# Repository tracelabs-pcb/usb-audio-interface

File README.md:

USB-C Audio Interface — Desktop / Streaming / Meetings

**Status: PCB-Design abgeschlossen — unbestückt**  
**Tool:** KiCad | **Layer:** 4-Layer | **Hersteller-ready:** Ja

---

## Projektbeschreibung

Kompaktes USB-C Audio-Interface für Desktop, Streaming und Meetings.
Wird am PC/Mac/Linux als Standard-USB-Audio-Device (UAC2) erkannt,
ohne Treiber. Entwickelt als reproduzierbarer Prototyp mit sauberem
Mixed-Signal-Layout (Analog + Digital).

**Besonderheiten:**
- USB Audio Class 2 (UAC2) — Plug & Play, treiberlos
- Stereo Kopfhörerverstärker mit I²C-Lautstärkeregelung (DirectPath)
- Elektret-Mikrofon-Bias + Hardware-Mute
- Rotary Encoder für Lautstärke + Mute
- Getrennte Digital/Analog-Versorgung (Buck → 3V3D → LDO → 3V3A)
- ESD-Schutz USB + Audio
- Testpunkte für alle kritischen Rails und Signale

---

## Hardware

| Komponente | Beschreibung |
|---|---|
| USB Audio Codec | PCM2912APJTR (ADC + DAC, USB-Enumeration integriert) |
| Kopfhörerverstärker | TPA6130A2RTJR (Stereo, I²C Volume, DirectPath/Capless) |
| Steuer-MCU | ATtiny1616 (Encoder, I²C, Button Handling) |
| Buck Converter | TPS62150A (5V → 3.3V Digital) |
| Analog LDO | TPS7A2033PDBVR (3.3V Digital → 3.3V Analog, Low-Noise) |
| ESD-Schutz | TPD4E05U06DQAR (USB, Audio, GPIO) |
| Stackup | 4-Layer (Signal / GND-Plane / Power / Signal+Pour) |
| Tool | KiCad |

---

## Anschlüsse

- USB-C  — Daten + Versorgung (Bus-Powered)
- TRRS 3.5mm Klinke CTIA (Headset: Mic + L/R + GND)
- Rotary Encoder (Lautstärke + Mute)
- LEDs: Power, Mic-Mute, Clip/Status
- I²C Header (OLED / Erweiterung)
- GPIO Header
- UPDI Header (ATtiny Programmierung)

---

## Architektur

**Versorgung:**
USB 5V → Buck (TPS62150A) → 3V3 Digital → LDO (TPS7A2033) → 3V3 Analog

**Signalführung:**
- USB D+/D− als Differential Pair
- Audio-Pfade kurz, getrennt von Digital
- Keine GND-Splits — gemeinsame GND-Plane (L2 durchgehend)

**Testpunkte:** 5V, 3V3D, 3V3A, GND, USB D+/D−, Audio-Nodes

---

## Ausschlüsse

Kein Serienprodukt — kein CE/EMV, keine Normenfreigabe,
keine sicherheitskritischen Funktionen.

---

## Dateien in diesem Repository

- `/kicad/` — KiCad Projektdateien
- `/screenshots/` — PCB- und Schematic-Ansichten

---

> Entwickelt von [Shawn Schneider](https://tracelabs-pcb.de)  
> — PCB-Design & Lötservice, Wolfsburg

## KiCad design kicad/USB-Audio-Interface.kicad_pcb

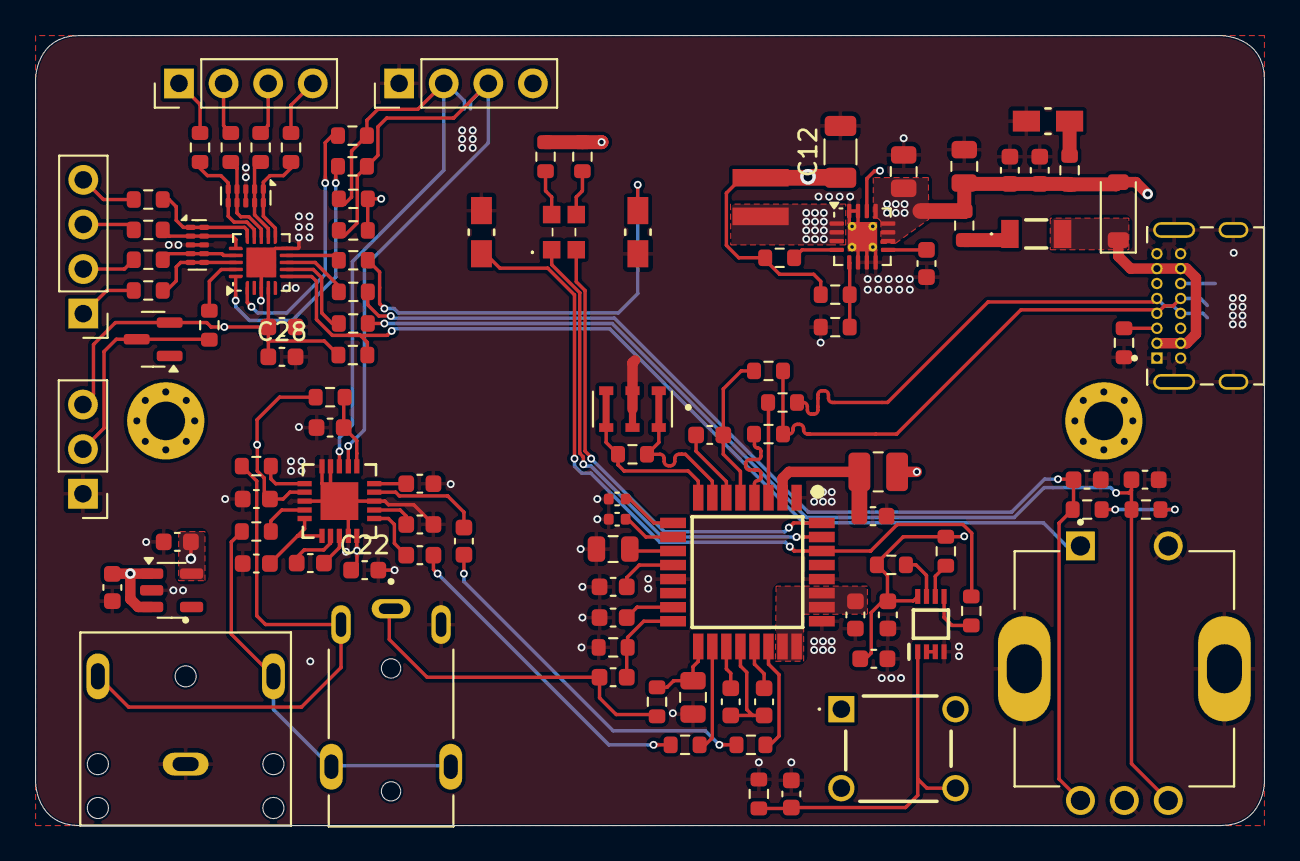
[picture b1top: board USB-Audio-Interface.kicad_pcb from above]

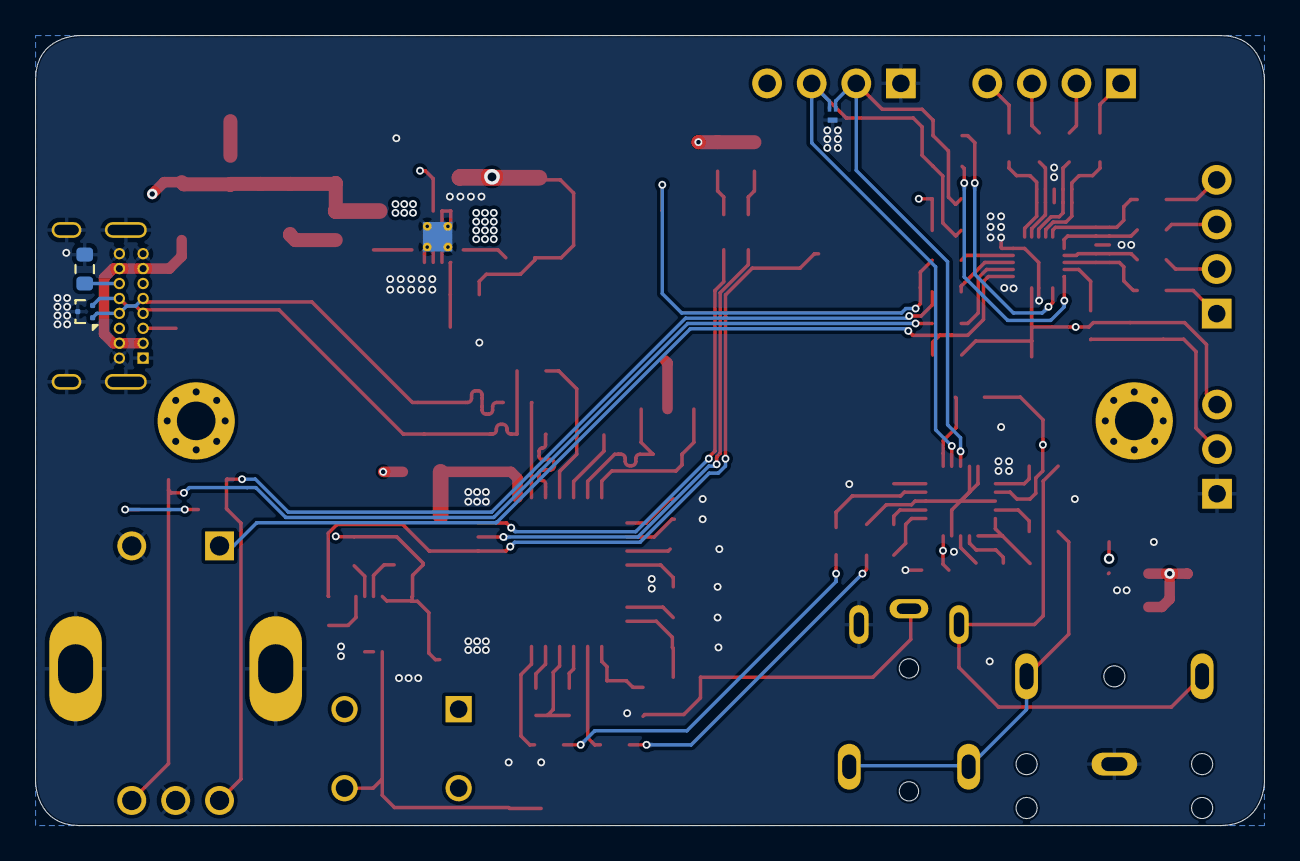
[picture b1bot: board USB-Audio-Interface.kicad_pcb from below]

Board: 4 copper layers, 70.0 x 45.0 mm, 108 parts (3 on the bottom side), 89 nets.

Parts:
C1, C2: 100pF; C_0402_1005Metric
C3, C21: 3,3µF; C_0805_2012Metric
C4, C22#2, C23, C24, C27, C33, C38: 100nF; C_0603_1608Metric
C5, C6, C7, C13, C14, C16, C17, C18, C19, C22, C28, C32, C37: 1µF; C_0603_1608Metric
C8, C36: 10µF; C_0805_2012Metric
C11: 3,3nF; C_0603_1608Metric
C12: 22µF; C_1206_3216Metric
C15: 1uF; C_0603_1608Metric
C20: 220nF; C_0603_1608Metric
C25, C26, C29, C31: 0,47µF; C_0603_1608Metric
C34, C35: 10nF; C_0603_1608Metric
CR1: PESD5V0X2UAMB; DFN10006B-3_SOT883B_NEX
D1, D4: RED; SM0805HCL_BIV
D3: BAT54A; SOT-23
D6: Littelfuse SMF5.0A; D_SOD-123
D7: Green_PWR; SM0805HCL_BIV
F1: MF-NSMF075/13X-2; MFNSMF07513X2
FB1: BLM18PG121SN1D; R_0603_1608Metric
IC1: PCM2912APJTR; QFP80P900X900X120-32N
IC2: TPS7A2033PDBVR; SOT-23-5
IC3: 74LVC1G74DC,125; SOP50P310X100-8N
J1: FC68125; CLIFF_FC68125
J3: SJ1-3523N; CUI_SJ1-3523N
J4: Conn_01x03_Pin; PinHeader_1x03_P2.54mm_Vertical
J5, J6, J7: Conn_01x04_Pin; PinHeader_1x04_P2.54mm_Vertical
J8: UJ20-C-H-G-SMT-TR; CUI_UJ20-C-H-G-SMT-TR
L1: 1µH; L_1008_2520Metric
L2: 2,2µH | WÜ 744028002; WE-TPC_282892
LED1: 150080RV54050
R1, R2, R23, R24: 22Ω; R_0603_1608Metric
R3, R4, R5: 1,5kΩ; R_0603_1608Metric
R8, R14, R19, R28: 100kΩ; R_0603_1608Metric
R9: 1,21MΩ; R_0603_1608Metric
R10: 383kΩ; R_0603_1608Metric
R11: 1MΩ; R_0603_1608Metric
R12, R13: 33Ω; R_0603_1608Metric
R15, R21: 4,7Ω; R_0603_1608Metric
R16: 2,2kΩ; R_0603_1608Metric
R17, R18, R29, R30, R33: 10kΩ; R_0603_1608Metric
R20, R22: 430Ω; R_0603_1608Metric
R25, R26, R27: 4,7kΩ; R_0603_1608Metric
R31, R32, R35, R36, R37, R38, R39, R40, R41, R42: 100Ω; R_0603_1608Metric
R43, R44: 5,1kΩ; R_0603_1608Metric
R45: 910Ω; R_0603_1608Metric
S2: PEC11R-4220F-S0024; XDCR_PEC11R-4220F-S0024
S3: TS02-66-120-BK-160-LCR-D; TS0266120BK160LCRD
U1: ATtiny1616-M; VQFN-20-1EP_3x3mm_P0.4mm_EP1.7x1.7mm
U2: TPA6130A2RTJR; QFN50P400X400X80-21N
U3: TPD2EUSB30; Texas_DRT-3
U4: TPS62150A; VQFN-16-1EP_3x3mm_P0.5mm_EP1.68x1.68mm_ThermalVias
U7, U8: TPD4E05U06DQA; USON-10_2.5x1.0mm_P0.5mm
Y1: CSTCR6M00G55Z-R0; OSC_CSTCR6M00G55Z-R0

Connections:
+5V: C8.1, C13.1, C36.1, C37.1, C38.1, D6.2 (A2), FB1.2, IC2.1 (IN), IC2.3 (EN), L1.1, R4.1, R5.1, R45.2, U4.10 (VIN), U4.11 (VIN), U4.12 (VIN), U4.13 (EN)
AUDIO_MUTE: R33.1, S2.1, U1.6 (PA5)
I2C_SCL_3V3: CR1.1, J5.2, R13.2, R27.1, U2.8 (SCL)
I2C_SDA_3V3: CR1.2, J5.3, R12.2, R26.1, U2.7 (SDA)
MCU_VCC: C12.1, C22#2.1, C23.1, C27.1, C28.1, D3.2, IC3.8 (VCC), J4.3, J5.4, L2.2, R8.1, R9.1, R17.1, R18.1, R26.2, R27.2, R29.2, R30.2, R33.2, S3.1, U1.4 (VCC), U4.14 (VOS)
MIC: C20.2, J1.1, R16.2
MMUTE: D1.2 (A), IC1.30 (MMUTE), R20.2
unnamed: D4.2 (A), R22.2
unnamed: D7.2 (A), R45.1
unnamed: F1.1, FB1.1
unnamed: IC1.4 (D+), R2.2
unnamed: IC1.3 (D-), R1.2
unnamed: C7.1, IC1.6 (DGND)
unnamed: C1.1, IC1.9 (FL)
unnamed: C2.1, IC1.10 (FR)
unnamed: C16.2, C17.1, IC1.20 (HGND)
unnamed: C21.1, IC1.17 (MBIAS), R16.1
unnamed: C6.1, IC1.2 (VBUS), L1.2
unnamed: C5.1, IC1.15 (VCCA)
unnamed: C17.2, IC1.19 (VCCL)
unnamed: C16.1, IC1.21 (VCCR)
unnamed: C3.1, IC1.11 (VCOM1)
unnamed: C4.1, IC1.12 (VCOM2)
unnamed: C7.2, IC1.5 (VDD), R3.2
unnamed: C20.1, IC1.16 (VIN), R28.2
unnamed: IC1.18 (VOUTL), R24.2
unnamed: IC1.22 (VOUTR), R23.2
unnamed: IC1.8 (XTI), R11.1, Y1.3
unnamed: IC1.7 (XTO), R11.2, Y1.1
unnamed: IC1.32 (~PLAY), LED1.2 (K_V)
unnamed: IC1.31 (~REC), LED1.1 (K_R)
unnamed: C24.1, IC3.1 (CP), R19.1, S3.4
unnamed: IC3.2 (D), IC3.3 (~Q)
unnamed: IC3.5 (Q), R20.1
unnamed: IC3.6 (~RD), R18.2
unnamed: IC3.7 (~SD), R17.2
unnamed: J6.1, R35.1
unnamed: J6.2, R36.1
unnamed: J6.3, R37.1
unnamed: J6.4, R38.1
unnamed: J7.1, R39.1
unnamed: J7.2, R40.1
unnamed: J7.3, R41.1
unnamed: J7.4, R42.1
unnamed: J8.A5 (CC1), R44.1
unnamed: J8.B5 (CC2), R43.1
unnamed: L2.1, U4.1 (SW), U4.2 (SW), U4.3 (SW)
unnamed: LED1.4 (A_R), R4.2
unnamed: LED1.3 (A_V), R5.2
unnamed: R12.1, U1.20 (PA1)
unnamed: R13.1, U1.1 (PA2)
unnamed: R31.1, U1.7 (PA6)
unnamed: R32.1, U1.8 (PA7)
unnamed: R22.1, U1.9 (PB5)
unnamed: R25.1, U1.19 (~RESET/PA0)
unnamed: C18.1, U2.17 (CPN)
unnamed: C18.2, U2.18 (CPP)
unnamed: C32.2, U2.15 (CPVSS_2), U2.16 (CPVSS)
unnamed: R21.1, U2.14 (HPLEFT)
unnamed: R15.2, U2.11 (HPRIGHT)
unnamed: C26.2, U2.1 (LEFTINM)
unnamed: C29.2, U2.2 (LEFTINP)
unnamed: C31.2, U2.5 (RIGHTINM)
unnamed: C25.2, U2.4 (RIGHTINP)
unnamed: C33.1, R14.1, U2.6 (~SD)
unnamed: R9.2, R10.1, U4.5 (FB)
unnamed: R8.2, U4.4 (PG)
unnamed: C11.1, U4.9 (SS/TR)
PB0: R35.2, U1.14 (PB0), U8.5 (D2-), U8.6 (NC)
PB1: R36.2, U1.13 (PB1), U8.4 (D2+), U8.7 (NC)
PB2: R37.2, U1.12 (PB2), U8.2 (D1-), U8.9 (NC)
PB3: R38.2, U1.11 (PB3), U8.1 (D1+), U8.10 (NC)
PC0: R42.2, U1.15 (PC0), U7.1 (D1+), U7.10 (NC)
PC1: R41.2, U1.16 (PC1), U7.2 (D1-), U7.9 (NC)
PC2: R40.2, U1.17 (PC2), U7.4 (D2+), U7.7 (NC)
PC3: R39.2, U1.18 (PC3), U7.5 (D2-), U7.6 (NC)
PCM2912A_POWER: C15.2, IC1.23 (MAMP), IC1.24 (POWER), IC1.26 (VCCP), IC1.27 (TEST1)
Rot_Enc_A: C34.1, R29.1, R32.2, S2.A
Rot_Enc_B: C35.1, R30.1, R31.2, S2.B
TPA6130A2_GND: C1.2, C2.2, C3.2, C4.2, C5.2, C6.2, C8.2, C11.2, C12.2, C13.2, C14.2, C15.1, C19.2, C21.2, C22.2, C22#2.2, C23.2, C24.2, C27.2, C28.2, C29.1, C31.1, C32.1, C33.2, C34.2, C35.2, C36.2, C37.2, C38.2, CR1.3, D1.1 (K), D4.1 (K), D7.1 (K), IC1.1 (BGND), IC1.13 (AGND), IC1.25 (PGND), IC1.28 (TEST0), IC2.2 (GND), IC3.4 (GND), J1.2, J3.1, J4.1, J5.1, J8.A1 (GND), J8.A12 (GND), J8.B1 (GND), J8.B12 (GND), J8.SH1 (SHIELD), J8.SH2 (SHIELD), J8.SH3 (SHIELD), J8.SH4 (SHIELD), R10.2, R19.2, R28.1, R43.2, R44.2, S2.2, S2.C (COM), S2.SH1 (SHIELD), S2.SH2 (SHIELD), U1.3 (GND), U1.10 (PB4), U1.21 (GND), U2.3 (GND_2), U2.9 (GND_3), U2.10 (GND_4), U2.13 (GND_5), U2.19 (GND), U2.21 (EP), U3.3 (GND), U4.6 (GND), U4.7 (FSW), U4.8 (DEF), U4.15 (GND), U4.16 (GND), U4.17 (GND), U7.3 (GND), U7.8 (GND), U8.3 (GND), U8.8 (GND), Y1.2
TPA6130A2_VDD: C14.1, C19.1, C22.1, IC2.5 (OUT), R14.2, U2.12 (VDD_2), U2.20 (VDD)
UPDI: D3.3, J4.2, R25.2
USB_D+: J8.A6 (DP1), J8.B6 (DP2), R2.1, R3.1, U3.2 (D-)
USB_D-: J8.A7 (DN1), J8.B7 (DN2), R1.1, U3.1 (D+)
VBUS: D6.1 (A1), F1.2, J8.A4 (VBUS), J8.A9 (VBUS), J8.B4 (VBUS), J8.B9 (VBUS)
Vout_L: J1.3_1, J1.3_2, J3.2, R21.2
Vout_L_PCM: C26.1, R24.1
Vout_R: J1.6, J3.3, R15.1
Vout_R_PCM: C25.1, R23.1

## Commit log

2026-03-24 Add USB audio interface project README
2026-03-24 Add screenshots folder
2026-03-24 Add project screenshots
2026-03-24 Add kicad folder
2026-03-24 Add KiCad project files
